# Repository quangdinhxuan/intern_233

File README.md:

CO3345 Intership at Xelex group from 30/5/2024 to 2/8/2024.

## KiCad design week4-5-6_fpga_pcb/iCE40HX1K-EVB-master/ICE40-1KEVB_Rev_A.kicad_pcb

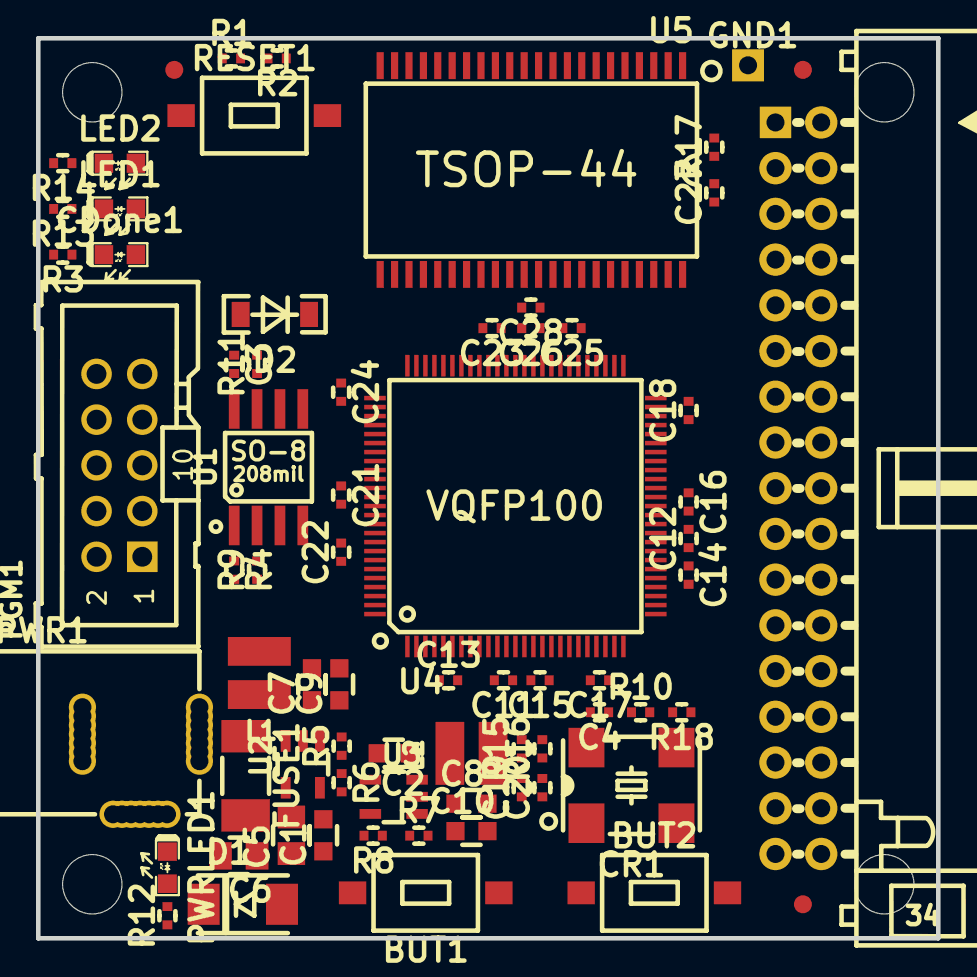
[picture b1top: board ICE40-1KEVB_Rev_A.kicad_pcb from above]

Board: 2 copper layers, 50.0 x 50.0 mm, 72 parts (0 on the bottom side), 91 nets, no tracks yet.

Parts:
BUT1, BUT2: T1107A(6x3,8x2,5MM)
C1, C2, C7, C8, C9, C10: 22uF/6.3V/0603; C_0603_5MIL_DWS
C3, C4, C11, C12, C13, C14, C15, C16, C17, C18, C21, C22, C23, C24, C25, C26, C27, C28: 100nF; C_0402_5MIL_DWS
C5, C6: 47uF/6.3V/0805; C_0805_5MIL_DWS
C19, C20: NA(100nF); C_0402_5MIL_DWS
CDone1: LED/Green/0603; LED_0603_KA
CR1: Oscillator-100MHZ_TXC-7W; Oscillator_7.0x5.0mm
D1: SMBJ6.0A; DO214AA
D2: 1N5819(S4SOD-123); SOD-123_1C-2A_KA
FUSE1: NA(5025); FUSE-5025
GND1: TESTPAD; TEST_PAD40x70_SQUARE
GPIO1: BH34R
L1, L2: 2.2uH/1.5A/DCR<0.1R/CD32; CD32
LED1, LED2: LED/Red/0603; LED_0603_KA
MountingHole: Mounting_hole_3.3mm
MountingHole#2, MountingHole#3, MountingHole#4: Mounting_hole_3.3mm
PGM1: BH10S; UEXT_ML10
PWR1: PWRJ-2mm(YDJ-1136); PWR_JACK_UNI_MILLING
PWRLED1: LED/Red/0603; LED_0603_KA
R1, R4, R11, R15, R16, R17: 10k; R_0402_5MIL_DWS
R2, R12, R13, R14: 2.2k; R_0402_5MIL_DWS
R3, R9, R10, R18: 22R; R_0402_5MIL_DWS
R5, R7, R8: 4.99k/1%; R_0402_5MIL_DWS
R6: 1.1k/1%; R_0402_5MIL_DWS
RESET1: T1107A(6x3,8x2,5MM)
U1: W25Q16BVSSIG(SOIC-8_208mil); SO-8_208mil
U2, U3: SY8009AAAC(SOT23-5); SOT-23-5
U4: ICE40HX1K-VQ100(VQFP100); VQFP100_Pitch-0.5mm_Dimensions-16.00x16.00x1.20mm
U5: K6R4016V1D-TC10(TSOP-44); TSOP-44_Pitch-0.80mm_18.80x11.80x1.20mm

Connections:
+1V2: C8.2, C10.2, C11.2, C12.2, C24.2, C26.2, L2.1, R7.2, U4.11, U4.35, U4.61, U4.77
+3V3: C3.2, C4.2, C7.2, C9.2, C13.2, C14.2, C15.2, C16.2, C17.2, C18.2, C21.2, C22.2, C23.2, C25.2, C27.2, C28.2, CR1.1, CR1.4, D2.2, GPIO1.3, L1.1, PGM1.1, R1.2, R2.2, R4.2, R5.2, R11.1, R15.2, R16.2, R17.1, U1.8, U4.6, U4.14, U4.22, U4.31, U4.38, U4.50, U4.58, U4.67, U4.88, U4.92, U5.11, U5.33
+5V: C1.2, C2.2, C5.2, C6.2, D1.C, FUSE1.1, FUSE1.2, GPIO1.1, PWR1.+, R12.1, U2.1, U2.4, U3.1, U3.4
/BUT1: BUT1.1, C19.2, R15.1, U4.41
/BUT2: BUT2.1, C20.2, R16.1, U4.42
/EXTCLK: GPIO1.6, R18.1
/LED1: GPIO1.10, LED1.2, U4.40
/LED2: GPIO1.12, LED2.2, U4.51
/PIO2_1: GPIO1.30, U4.26
/PIO2_2: GPIO1.28, U4.27
/PIO2_3: GPIO1.26, U4.28
/PIO2_4: GPIO1.24, U4.29
/PIO2_5: GPIO1.22, U4.30
/PIO2_6: GPIO1.20, U4.33
/PIO2_7: GPIO1.18, U4.34
/PIO2_8: GPIO1.16, U4.36
/PIO2_9: GPIO1.14, U4.37
/PIO3_1A: GPIO1.5, U4.1
/PIO3_1B: GPIO1.7, U4.2
/PIO3_2A: GPIO1.9, U4.3
/PIO3_2B: GPIO1.11, U4.4
/PIO3_3A: GPIO1.13, U4.7
/PIO3_3B: GPIO1.15, U4.8
/PIO3_5A: GPIO1.17, U4.9
/PIO3_5B: GPIO1.19, U4.10
/PIO3_6A: GPIO1.21, U4.12
/PIO3_6B: GPIO1.23, U4.13
/PIO3_7B: GPIO1.25, U4.16
/PIO3_8A: GPIO1.27, U4.18
/PIO3_8B: GPIO1.29, U4.19
/PIO3_10A: GPIO1.31, U4.20
/PIO3_10B: GPIO1.33, U4.21
/PIO3_12A: GPIO1.34, U4.24
/PIO3_12B: GPIO1.32, U4.25
/SA0: U4.79, U5.1
/SA1: U4.80, U5.2
/SA2: U4.81, U5.3
/SA3: U4.82, U5.4
/SA4: U4.83, U5.5
/SA5: U4.85, U5.18
/SA6: U4.86, U5.19
/SA7: U4.87, U5.20
/SA8: U4.89, U5.21
/SA9: U4.90, U5.22
/SA10: U4.91, U5.23
/SA11: U4.93, U5.24
/SA12: U4.94, U5.25
/SA13: U4.95, U5.26
/SA14: U4.96, U5.27
/SA15: U4.97, U5.42
/SA16: U4.99, U5.43
/SA17: U4.100, U5.44
/SD0: U4.62, U5.7
/SD1: U4.63, U5.8
/SD2: U4.64, U5.9
/SD3: U4.65, U5.10
/SD4: U4.66, U5.13
/SD5: U4.68, U5.14
/SD6: U4.69, U5.15
/SD7: U4.71, U5.16
/SD8: U4.72, U5.29
/SD9: U4.60, U5.30
/SD10: U4.59, U5.31
/SD11: U4.57, U5.32
/SD12: U4.56, U5.35
/SD13: U4.54, U5.36
/SD14: U4.53, U5.37
/SD15: U4.52, U5.38
/SRAM_#CS: R17.2, U4.78, U5.6
/SRAM_#OE: U4.74, U5.41
/SRAM_#WE: U4.73, U5.17
/SYSCLK: R10.1, U4.15
/iCE40-CDONE: CDone1.2, PGM1.5, R2.1, U4.43
/iCE40-CRESET: PGM1.6, R1.1, RESET1.1, U4.44
/iCE40-SCK: PGM1.9, U1.6, U4.48
/iCE40-SDI: PGM1.8, U1.2, U4.46
/iCE40-SDO: PGM1.7, U1.5, U4.45
/iCE40-SS_B: PGM1.10, R9.1, U4.49
GND: BUT1.2, BUT2.2, C1.1, C2.1, C3.1, C4.1, C5.1, C6.1, C7.1, C8.1, C9.1, C10.1, C11.1, C12.1, C13.1, C14.1, C15.1, C16.1, C17.1, C18.1, C19.1, C20.1, C21.1, C22.1, C23.1, C24.1, C25.1, C26.1, C27.1, C28.1, CR1.2, D1.A, GND1.1, GPIO1.2, GPIO1.4, GPIO1.8, PGM1.2, PWR1.-, PWRLED1.1, R3.2, R6.2, R8.2, R13.2, R14.2, RESET1.2, U1.4, U2.2, U3.2, U4.5, U4.17, U4.23, U4.32, U4.39, U4.47, U4.55, U4.70, U4.84, U4.98, U5.12, U5.34, U5.39, U5.40
unnamed: CDone1.1, R3.1
unnamed: CR1.3, R10.2, R18.2
unnamed: D2.1, U4.75
unnamed: L1.2, U2.3
unnamed: L2.2, U3.3
unnamed: LED1.1, R13.1
unnamed: LED2.1, R14.1
unnamed: PWRLED1.2, R12.2
unnamed: R4.1, R9.2, U1.1
unnamed: R5.1, R6.1, U2.5
unnamed: R7.1, R8.1, U3.5
unnamed: R11.2, U1.3, U1.7

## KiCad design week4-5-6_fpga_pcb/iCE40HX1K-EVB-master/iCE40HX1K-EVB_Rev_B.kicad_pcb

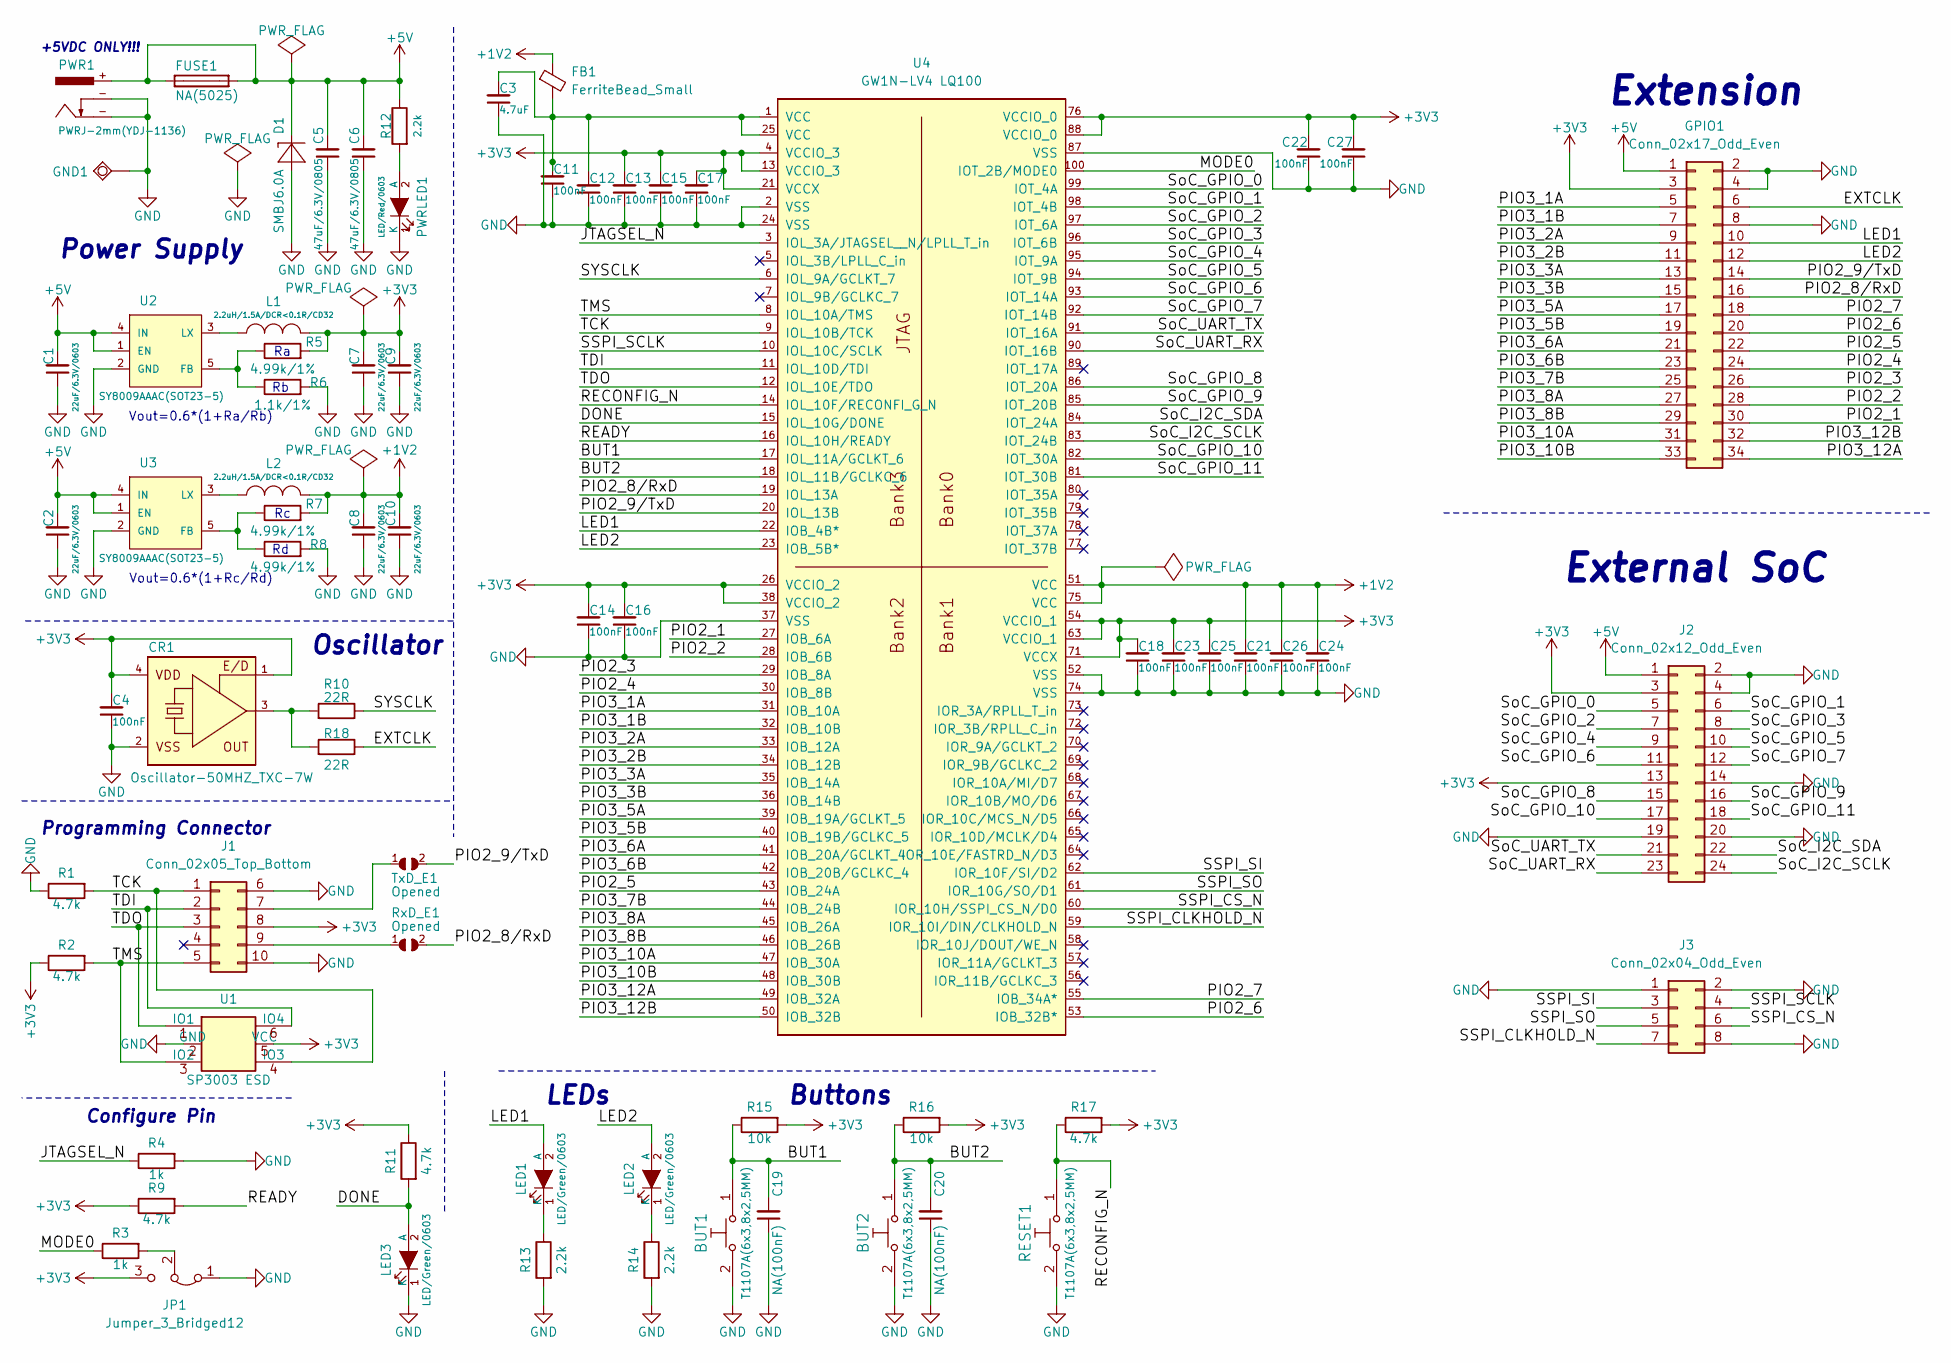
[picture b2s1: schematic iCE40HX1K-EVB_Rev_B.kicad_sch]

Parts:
BUT1, BUT2: T1107A(6x3,8x2,5MM)
C1, C2, C7, C8, C9, C10: 22uF/6.3V/0603; C_0603_5MIL_DWS
C3: 4.7uF; C_0402_5MIL_DWS
C4, C11, C12, C13, C14, C15, C16, C17, C18, C21, C22, C23, C24, C25, C26, C27: 100nF; C_0402_5MIL_DWS
C5, C6: 47uF/6.3V/0805; C_0805_5MIL_DWS
C19, C20: NA(100nF); C_0402_5MIL_DWS
CR1: Oscillator-50MHZ_TXC-7W; Oscillator_7.0x5.0mm
D1: SMBJ6.0A; DO214AA
FB1: FerriteBead_Small; Fuse_0603_1608Metric_Pad1.05x0.95mm_HandSolder
FUSE1: NA(5025); FUSE-5025
GND1: TESTPAD; TEST_PAD40x70_SQUARE
GPIO1: Conn_02x17_Odd_Even; PinHeader_2x17_P2.54mm_Horizontal
J1: Conn_02x05_Top_Bottom; PinHeader_2x06_P2.54mm_Vertical
J2: Conn_02x12_Odd_Even; PinHeader_2x12_P2.54mm_Vertical
J3: Conn_02x04_Odd_Even; PinHeader_2x04_P2.54mm_Vertical
JP1: Jumper_3_Bridged12; SolderJumper-3_P1.3mm_Open_Pad1.0x1.5mm
L1, L2: 2.2uH/1.5A/DCR<0.1R/CD32; CD32
LED1, LED2, LED3: LED/Green/0603; LED_0603_KA
PWR1: PWRJ-2mm(YDJ-1136)
PWRLED1: LED/Red/0603; LED_0603_KA
R1, R2, R9, R11, R17: 4.7k; R_0402_5MIL_DWS
R3, R4: 1k; R_0402_5MIL_DWS
R5, R7, R8: 4.99k/1%; R_0402_5MIL_DWS
R6: 1.1k/1%; R_0402_5MIL_DWS
R10, R18: 22R; R_0402_5MIL_DWS
R12, R13, R14: 2.2k; R_0402_5MIL_DWS
R15, R16: 10k; R_0402_5MIL_DWS
RESET1: T1107A(6x3,8x2,5MM)
RxD_E1: Opened; SJ
TxD_E1: Opened; SJ
U1: SP3003 ESD; SOT-23-6
U2, U3: SY8009AAAC(SOT23-5); SOT-23-5
U4: GW1N-LV4 LQ100; LQFP-100_14x14mm_P0.5mm

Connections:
+1V2: C8.2, C10.2, C21.2, C24.2, C26.2, FB1.1, L2.1, R7.2, U4.51 (VCC), U4.75 (VCC)
+3V3: C4.2, C7.2, C9.2, C13.2, C14.2, C15.2, C16.2, C17.2, C18.2, C22.2, C23.2, C25.2, C27.2, CR1.1 (E/D), CR1.4 (VDD), GPIO1.3, J1.8, J2.3, J2.13, JP1.3 (B), L1.1, R2.1, R5.2, R9.1, R11.1, R15.2, R16.2, R17.2, U1.5 (VCC), U4.4 (VCCIO_3), U4.13 (VCCIO_3), U4.21 (VCCX), U4.26 (VCCIO_2), U4.38 (VCCIO_2), U4.54 (VCCIO_1), U4.63 (VCCIO_1), U4.71 (VCCX), U4.76 (VCCIO_0), U4.88 (VCCIO_0)
+5V: C1.2, C2.2, C5.2, C6.2, D1.C, FUSE1.1, FUSE1.2, GPIO1.1, J2.1, PWR1.+, R12.1, U2.1 (EN), U2.4 (IN), U3.1 (EN), U3.4 (IN)
/BUT1: BUT1.1, C19.2, R15.1, U4.17 (IOL_11A/GCLKT_6)
/BUT2: BUT2.1, C20.2, R16.1, U4.18 (IOL_11B/GCLKC_6)
/DONE: LED3.2 (A), R11.2, U4.15 (IOL_10G/DONE)
/EXTCLK: GPIO1.6, R18.1
/JTAGSEL_N: R4.1, U4.3 (IOL_3A/JTAGSEL__N/LPLL_T_in)
/LED1: GPIO1.10, LED1.2 (A), U4.22 (IOB_4B*)
/LED2: GPIO1.12, LED2.2 (A), U4.23 (IOB_5B*)
/MODE0: R3.1, U4.100 (IOT_2B/MODE0)
/PIO2_1: GPIO1.30, U4.27 (IOB_6A)
/PIO2_2: GPIO1.28, U4.28 (IOB_6B)
/PIO2_3: GPIO1.26, U4.29 (IOB_8A)
/PIO2_4: GPIO1.24, U4.30 (IOB_8B)
/PIO2_5: GPIO1.22, U4.43 (IOB_24A)
/PIO2_6: GPIO1.20, U4.53 (IOB_32B*)
/PIO2_7: GPIO1.18, U4.55 (IOB_34A*)
/PIO2_8/RxD: GPIO1.16, RxD_E1.2, U4.19 (IOL_13A)
/PIO2_9/TxD: GPIO1.14, TxD_E1.2, U4.20 (IOL_13B)
/PIO3_1A: GPIO1.5, U4.31 (IOB_10A)
/PIO3_1B: GPIO1.7, U4.32 (IOB_10B)
/PIO3_2A: GPIO1.9, U4.33 (IOB_12A)
/PIO3_2B: GPIO1.11, U4.34 (IOB_12B)
/PIO3_3A: GPIO1.13, U4.35 (IOB_14A)
/PIO3_3B: GPIO1.15, U4.36 (IOB_14B)
/PIO3_5A: GPIO1.17, U4.39 (IOB_19A/GCLKT_5)
/PIO3_5B: GPIO1.19, U4.40 (IOB_19B/GCLKC_5)
/PIO3_6A: GPIO1.21, U4.41 (IOB_20A/GCLKT_4)
/PIO3_6B: GPIO1.23, U4.42 (IOB_20B/GCLKC_4)
/PIO3_7B: GPIO1.25, U4.44 (IOB_24B)
/PIO3_8A: GPIO1.27, U4.45 (IOB_26A)
/PIO3_8B: GPIO1.29, U4.46 (IOB_26B)
/PIO3_10A: GPIO1.31, U4.47 (IOB_30A)
/PIO3_10B: GPIO1.33, U4.48 (IOB_30B)
/PIO3_12A: GPIO1.34, U4.49 (IOB_32A)
/PIO3_12B: GPIO1.32, U4.50 (IOB_32B)
/READY: R9.2, U4.16 (IOL_10H/READY)
/RECONFIG_N: R17.1, RESET1.1, U4.14 (IOL_10F/RECONFI_G_N)
/SSPI_CLKHOLD_N: J3.7, U4.59 (IOR_10I/DIN/CLKHOLD_N)
/SSPI_CS_N: J3.6, U4.60 (IOR_10H/SSPI_CS_N/D0)
/SSPI_SCLK: J3.4, U4.10 (IOL_10C/SCLK)
/SSPI_SI: J3.3, U4.62 (IOR_10F/SI/D2)
/SSPI_SO: J3.5, U4.61 (IOR_10G/SO/D1)
/SYSCLK: R10.1, U4.6 (IOL_9A/GCLKT_7)
/SoC_GPIO_0: J2.5, U4.99 (IOT_4A)
/SoC_GPIO_1: J2.6, U4.98 (IOT_4B)
/SoC_GPIO_2: J2.7, U4.97 (IOT_6A)
/SoC_GPIO_3: J2.8, U4.96 (IOT_6B)
/SoC_GPIO_4: J2.9, U4.95 (IOT_9A)
/SoC_GPIO_5: J2.10, U4.94 (IOT_9B)
/SoC_GPIO_6: J2.11, U4.93 (IOT_14A)
/SoC_GPIO_7: J2.12, U4.92 (IOT_14B)
/SoC_GPIO_8: J2.15, U4.86 (IOT_20A)
/SoC_GPIO_9: J2.16, U4.85 (IOT_20B)
/SoC_GPIO_10: J2.17, U4.82 (IOT_30A)
/SoC_GPIO_11: J2.18, U4.81 (IOT_30B)
/SoC_I2C_SCLK: J2.24, U4.83 (IOT_24B)
/SoC_I2C_SDA: J2.22, U4.84 (IOT_24A)
/SoC_UART_RX: J2.23, U4.90 (IOT_16B)
/SoC_UART_TX: J2.21, U4.91 (IOT_16A)
/TCK: J1.1, R1.2, U1.4 (IO3), U4.9 (IOL_10B/TCK)
/TDI: J1.2, U1.6 (IO4), U4.11 (IOL_10D/TDI)
/TDO: J1.3, U1.1 (IO1), U4.12 (IOL_10E/TDO)
/TMS: J1.5, R2.2, U1.3 (IO2), U4.8 (IOL_10A/TMS)
GND: BUT1.2, BUT2.2, C1.1, C2.1, C3.1, C4.1, C5.1, C6.1, C7.1, C8.1, C9.1, C10.1, C11.1, C12.1, C13.1, C14.1, C15.1, C16.1, C17.1, C18.1, C19.1, C20.1, C21.1, C22.1, C23.1, C24.1, C25.1, C26.1, C27.1, CR1.2 (VSS), D1.A, GND1.1 (Pad), GPIO1.2, GPIO1.4, GPIO1.8, J1.6, J1.10, J2.2, J2.4, J2.14, J2.19, J2.20, J3.1, J3.2, J3.8, JP1.1 (A), LED3.1 (K), PWR1.-, PWRLED1.1 (K), R1.1, R4.2, R6.2, R8.2, R13.2, R14.2, RESET1.2, U1.2 (GND), U2.2 (GND), U3.2 (GND), U4.2 (VSS), U4.24 (VSS), U4.37 (VSS), U4.52 (VSS), U4.74 (VSS), U4.87 (VSS)
unnamed: C3.2, C11.2, C12.2, FB1.2, U4.1 (VCC), U4.25 (VCC)
unnamed: CR1.3 (OUT), R10.2, R18.2
unnamed: J1.7, TxD_E1.1
unnamed: J1.9, RxD_E1.1
unnamed: JP1.2 (C), R3.2
unnamed: LED1.1 (K), R13.1
unnamed: LED2.1 (K), R14.1
unnamed: PWRLED1.2 (A), R12.2
unnamed: R5.1, R6.1, U2.5 (FB)
unnamed: L1.2, U2.3 (LX)
unnamed: R7.1, R8.1, U3.5 (FB)
unnamed: L2.2, U3.3 (LX)

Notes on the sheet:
Programming Connector
LEDs
Extension
Vout=0.6*(1+Ra/Rb)
Oscillator
Vout=0.6*(1+Rc/Rd)
Power Supply
+5VDC ONLY!!!
Buttons
Configure Pin
External SoC

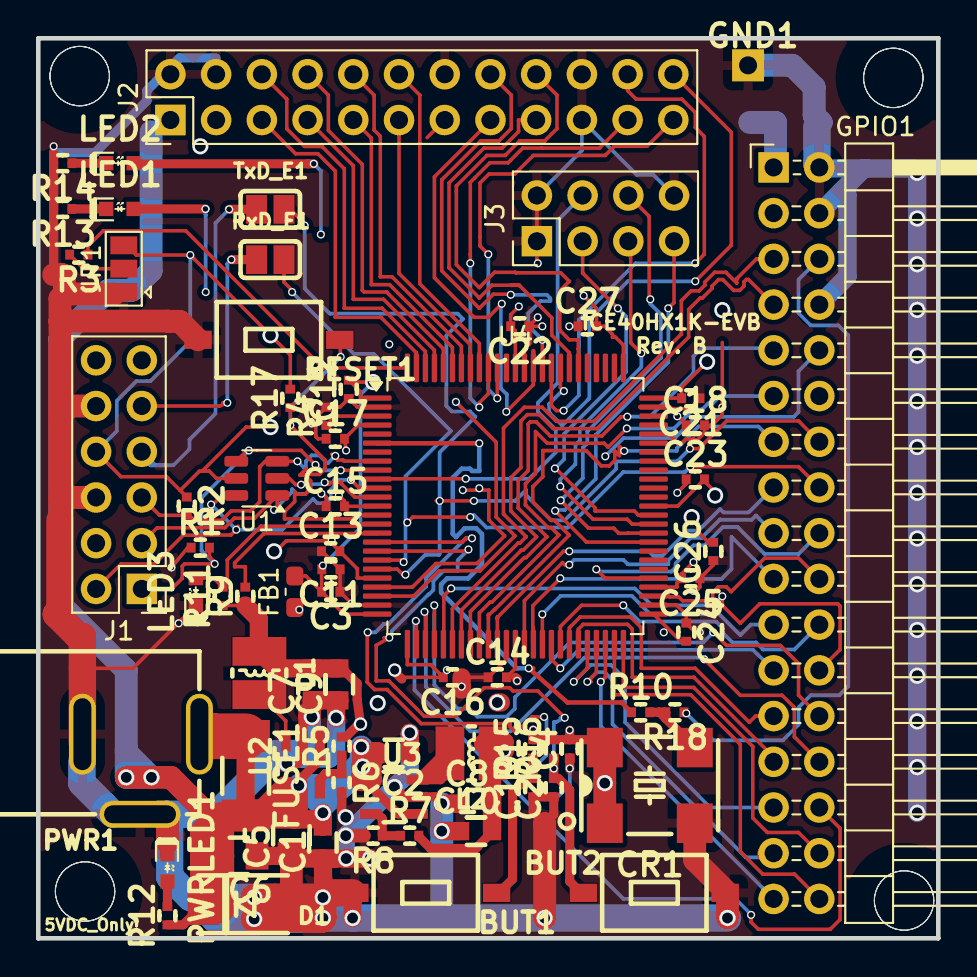
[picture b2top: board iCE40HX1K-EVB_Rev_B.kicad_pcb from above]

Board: 4 copper layers, 50.0 x 50.0 mm, 75 parts (0 on the bottom side), 78 nets.

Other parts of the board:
MountingHole: Mounting_hole_3.3mm
MountingHole#2, MountingHole#3, MountingHole#4: Mounting_hole_3.3mm

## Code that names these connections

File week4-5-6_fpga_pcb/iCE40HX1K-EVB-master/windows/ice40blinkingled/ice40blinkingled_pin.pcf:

set_io CLK 15
set_io BUT1 41
set_io BUT2 42
set_io LED1 40
set_io LED2 51

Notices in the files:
week4-5-6_fpga_pcb/iCE40HX1K-EVB-master/ICE40-1KEVB_Rev_A.kicad_pcb:
(C) 2016
